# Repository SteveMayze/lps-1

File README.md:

# Solar Power Sensor LPS-1

A simple remote sensing node to monitor the voltage and load current for a solar/battery unit.
This unit brings together the prototype projects [Gateway Node](https://github.com/SteveMayze/leawood_gateway),  [Atmega1608 Development board](https://github.com/SteveMayze/atmega1608_dev) and [Sensor node firmware (Atmega1608 and INA219)](https://github.com/SteveMayze/PowerSensor-Atmega1608) to create a unified PCB that can be deployed to the field to make a connection to the gateway project in order to transfer the sensor data to the internet.

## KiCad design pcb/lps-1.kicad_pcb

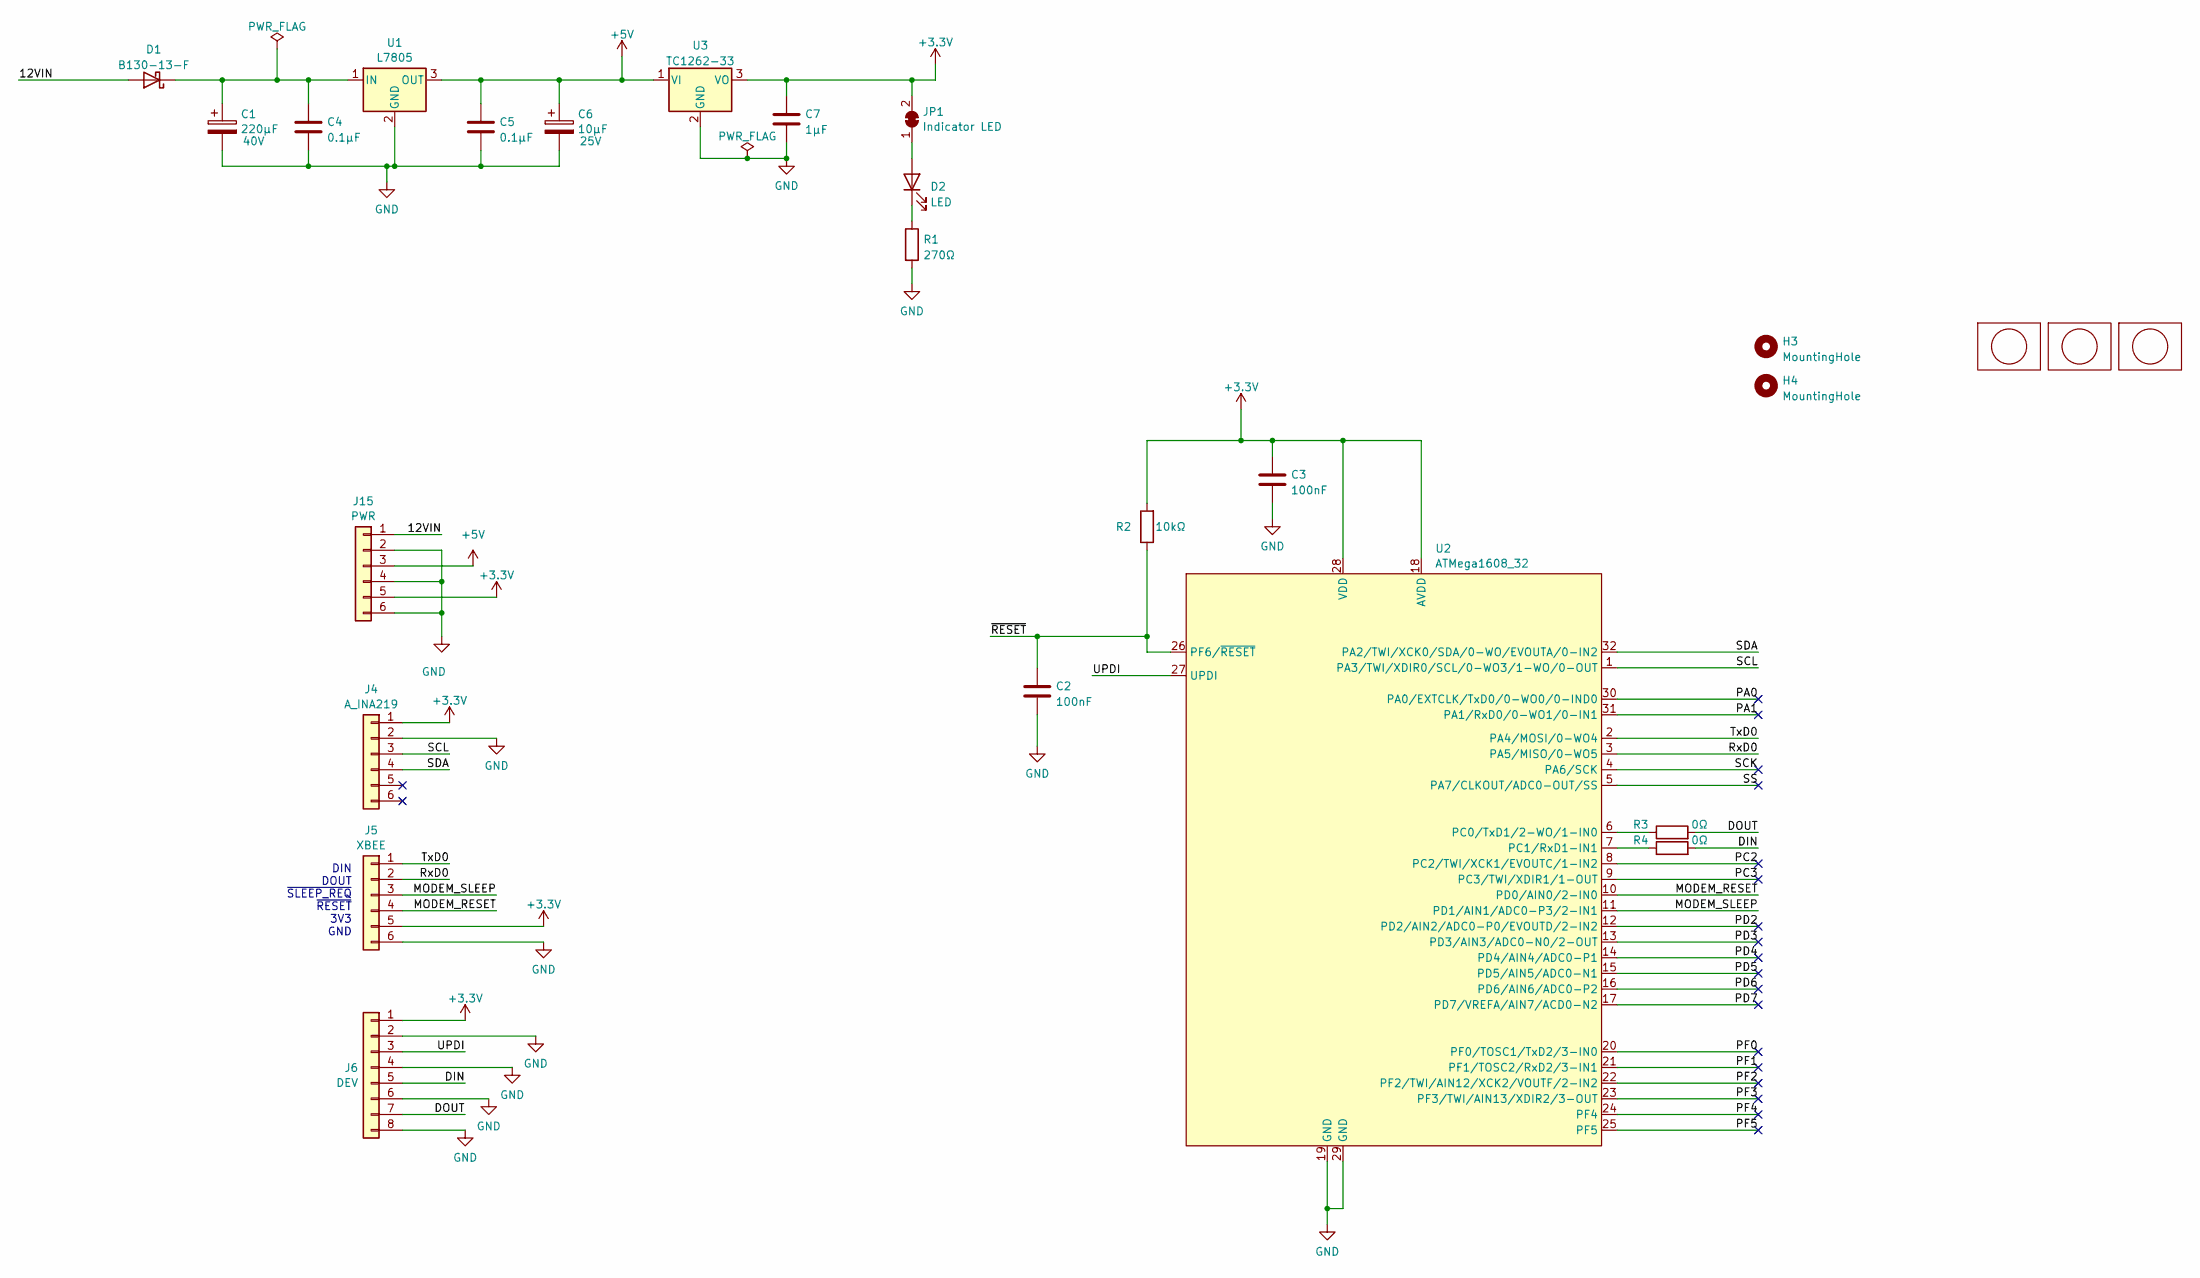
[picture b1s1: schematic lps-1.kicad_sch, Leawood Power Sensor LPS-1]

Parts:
C1: 220μF; CP_Radial_D10.0mm_P2.50mm; Voltage 40V
C2, C3: 100nF; C_0805_2012Metric
C4, C5: 0.1μF; C_0805_2012Metric_Pad1.18x1.45mm_HandSolder
C6: 10μF; CP_Radial_D5.0mm_P2.50mm; Voltage 25V
C7: 1μF; C_0805_2012Metric_Pad1.18x1.45mm_HandSolder
D1: B130-13-F; D_SMA; MPN B130-13-F
D2: LED; LED_0805_2012Metric
H3, H4: MountingHole; MountingHole_2.7mm_M2.5
J4: A_INA219; Adafruit-INA219_2xM2.5
J5: XBEE; PinHeader_2x03_P2.54mm_Vertical
J6: DEV; PinHeader_1x08_P2.54mm_Vertical
J15: PWR; PinHeader_1x06_P2.54mm_Vertical
JP1: Indicator LED; SolderJumper-2_P1.3mm_Bridged_RoundedPad1.0x1.5mm
Lg1, Lg2: logo; MyBasic_rounded_50_1
Lg3: logo; KiCad-Logo_5mm_SilkScreen
R1: 270Ω; R_0805_2012Metric
R2: 10kΩ; R_0805_2012Metric
R3, R4: 0Ω; R_0805_2012Metric
U1: L7805; TO-220-3_Vertical
U2: ATMega1608_32; TQFP-32_7x7mm_P0.8mm
U3: TC1262-33; SOT-223-3_TabPin2

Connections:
+3.3V: C3.1, C7.1, J4.1, J5.5, J6.1, J15.5, JP1.2 (B), R2.2, U2.18 (AVDD), U2.28 (VDD), U3.3 (VO)
+5V: C5.1, C6.1, J15.3, U1.3 (OUT), U3.1 (VI)
/12VIN: D1.2 (A), J15.1
/DIN: J6.5, R4.2
/DOUT: J6.7, R3.2
/MODEM_RESET: J5.4, U2.10 (PD0/AIN0/2-IN0)
/MODEM_SLEEP: J5.3, U2.11 (PD1/AIN1/ADC0-P3/2-IN1)
/PA0: U2.30 (PA0/EXTCLK/TxD0/0-WO0/0-IND0)
/PA1: U2.31 (PA1/RxD0/0-WO1/0-IN1)
/PC2: U2.8 (PC2/TWI/XCK1/EVOUTC/1-IN2)
/PC3: U2.9 (PC3/TWI/XDIR1/1-OUT)
/PD2: U2.12 (PD2/AIN2/ADC0-P0/EVOUTD/2-IN2)
/PD3: U2.13 (PD3/AIN3/ADC0-N0/2-OUT)
/PD4: U2.14 (PD4/AIN4/ADC0-P1)
/PD5: U2.15 (PD5/AIN5/ADC0-N1)
/PD6: U2.16 (PD6/AIN6/ADC0-P2)
/PD7: U2.17 (PD7/VREFA/AIN7/ACD0-N2)
/PF0: U2.20 (PF0/TOSC1/TxD2/3-IN0)
/PF1: U2.21 (PF1/TOSC2/RxD2/3-IN1)
/PF2: U2.22 (PF2/TWI/AIN12/XCK2/VOUTF/2-IN2)
/PF3: U2.23 (PF3/TWI/AIN13/XDIR2/3-OUT)
/PF4: U2.24 (PF4)
/PF5: U2.25 (PF5)
/RxD0: J5.2, U2.3 (PA5/MISO/0-WO5)
/SCK: U2.4 (PA6/SCK)
/SCL: J4.3, U2.1 (PA3/TWI/XDIR0/SCL/0-WO3/1-WO/0-OUT)
/SDA: J4.4, U2.32 (PA2/TWI/XCK0/SDA/0-WO/EVOUTA/0-IN2)
/SS: U2.5 (PA7/CLKOUT/ADC0-OUT/SS)
/TxD0: J5.1, U2.2 (PA4/MOSI/0-WO4)
/UPDI: J6.3, U2.27 (UPDI)
/~RESET: C2.1, R2.1, U2.26 (PF6/~RESET)
GND: C1.2, C2.2, C3.2, C4.2, C5.2, C6.2, C7.2, J4.2, J5.6, J6.2, J6.4, J6.6, J6.8, J15.2, J15.4, J15.6, R1.2, U1.2 (GND), U2.19 (GND), U2.29 (GND), U3.2 (GND)
unnamed: C1.1, C4.1, D1.1 (K), U1.1 (IN)
unnamed: D2.2 (A), JP1.1 (A)
unnamed: D2.1 (K), R1.1
unnamed: R3.1, U2.6 (PC0/TxD1/2-WO/1-IN0)
unnamed: R4.1, U2.7 (PC1/RxD1-IN1)

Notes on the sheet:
DIN DOUT ~{SLEEP_REQ} ~{RESET} 3V3 GND

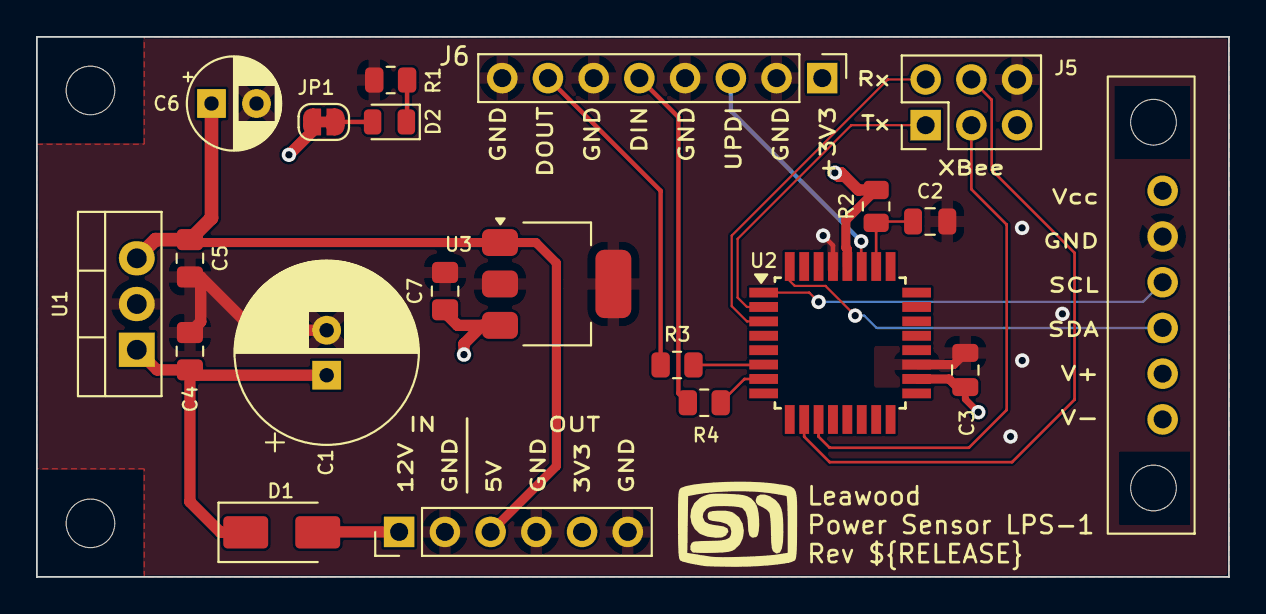
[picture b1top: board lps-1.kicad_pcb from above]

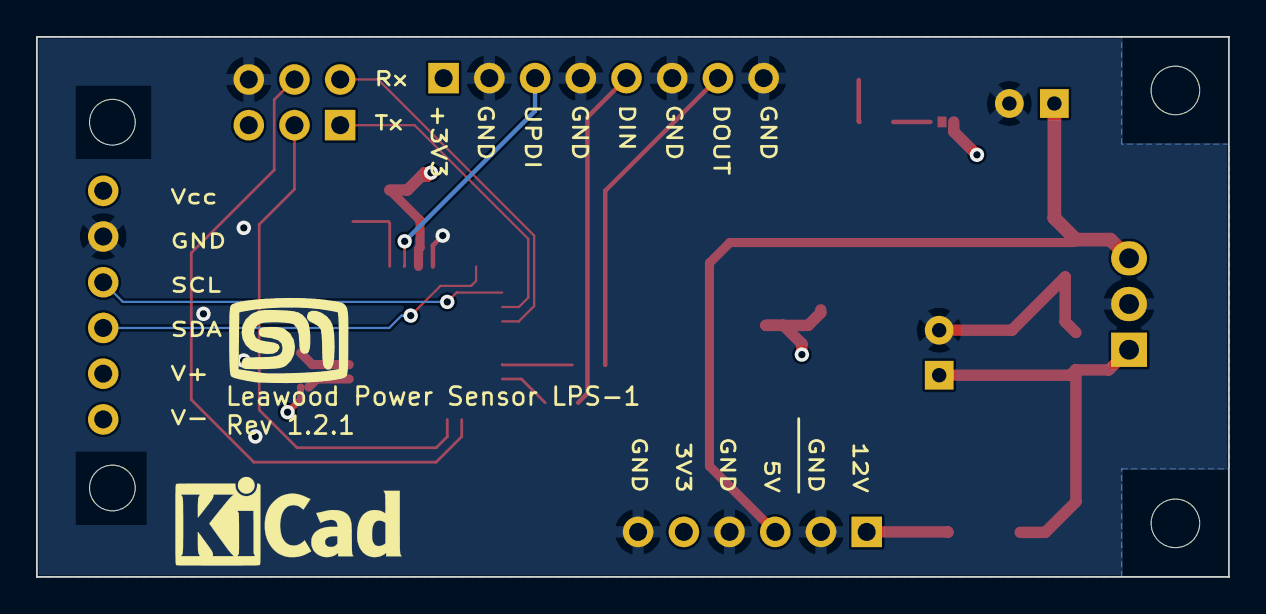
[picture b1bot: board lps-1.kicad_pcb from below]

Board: 4 copper layers, 66.2 x 30.0 mm, 26 parts (2 on the bottom side), 19 nets.

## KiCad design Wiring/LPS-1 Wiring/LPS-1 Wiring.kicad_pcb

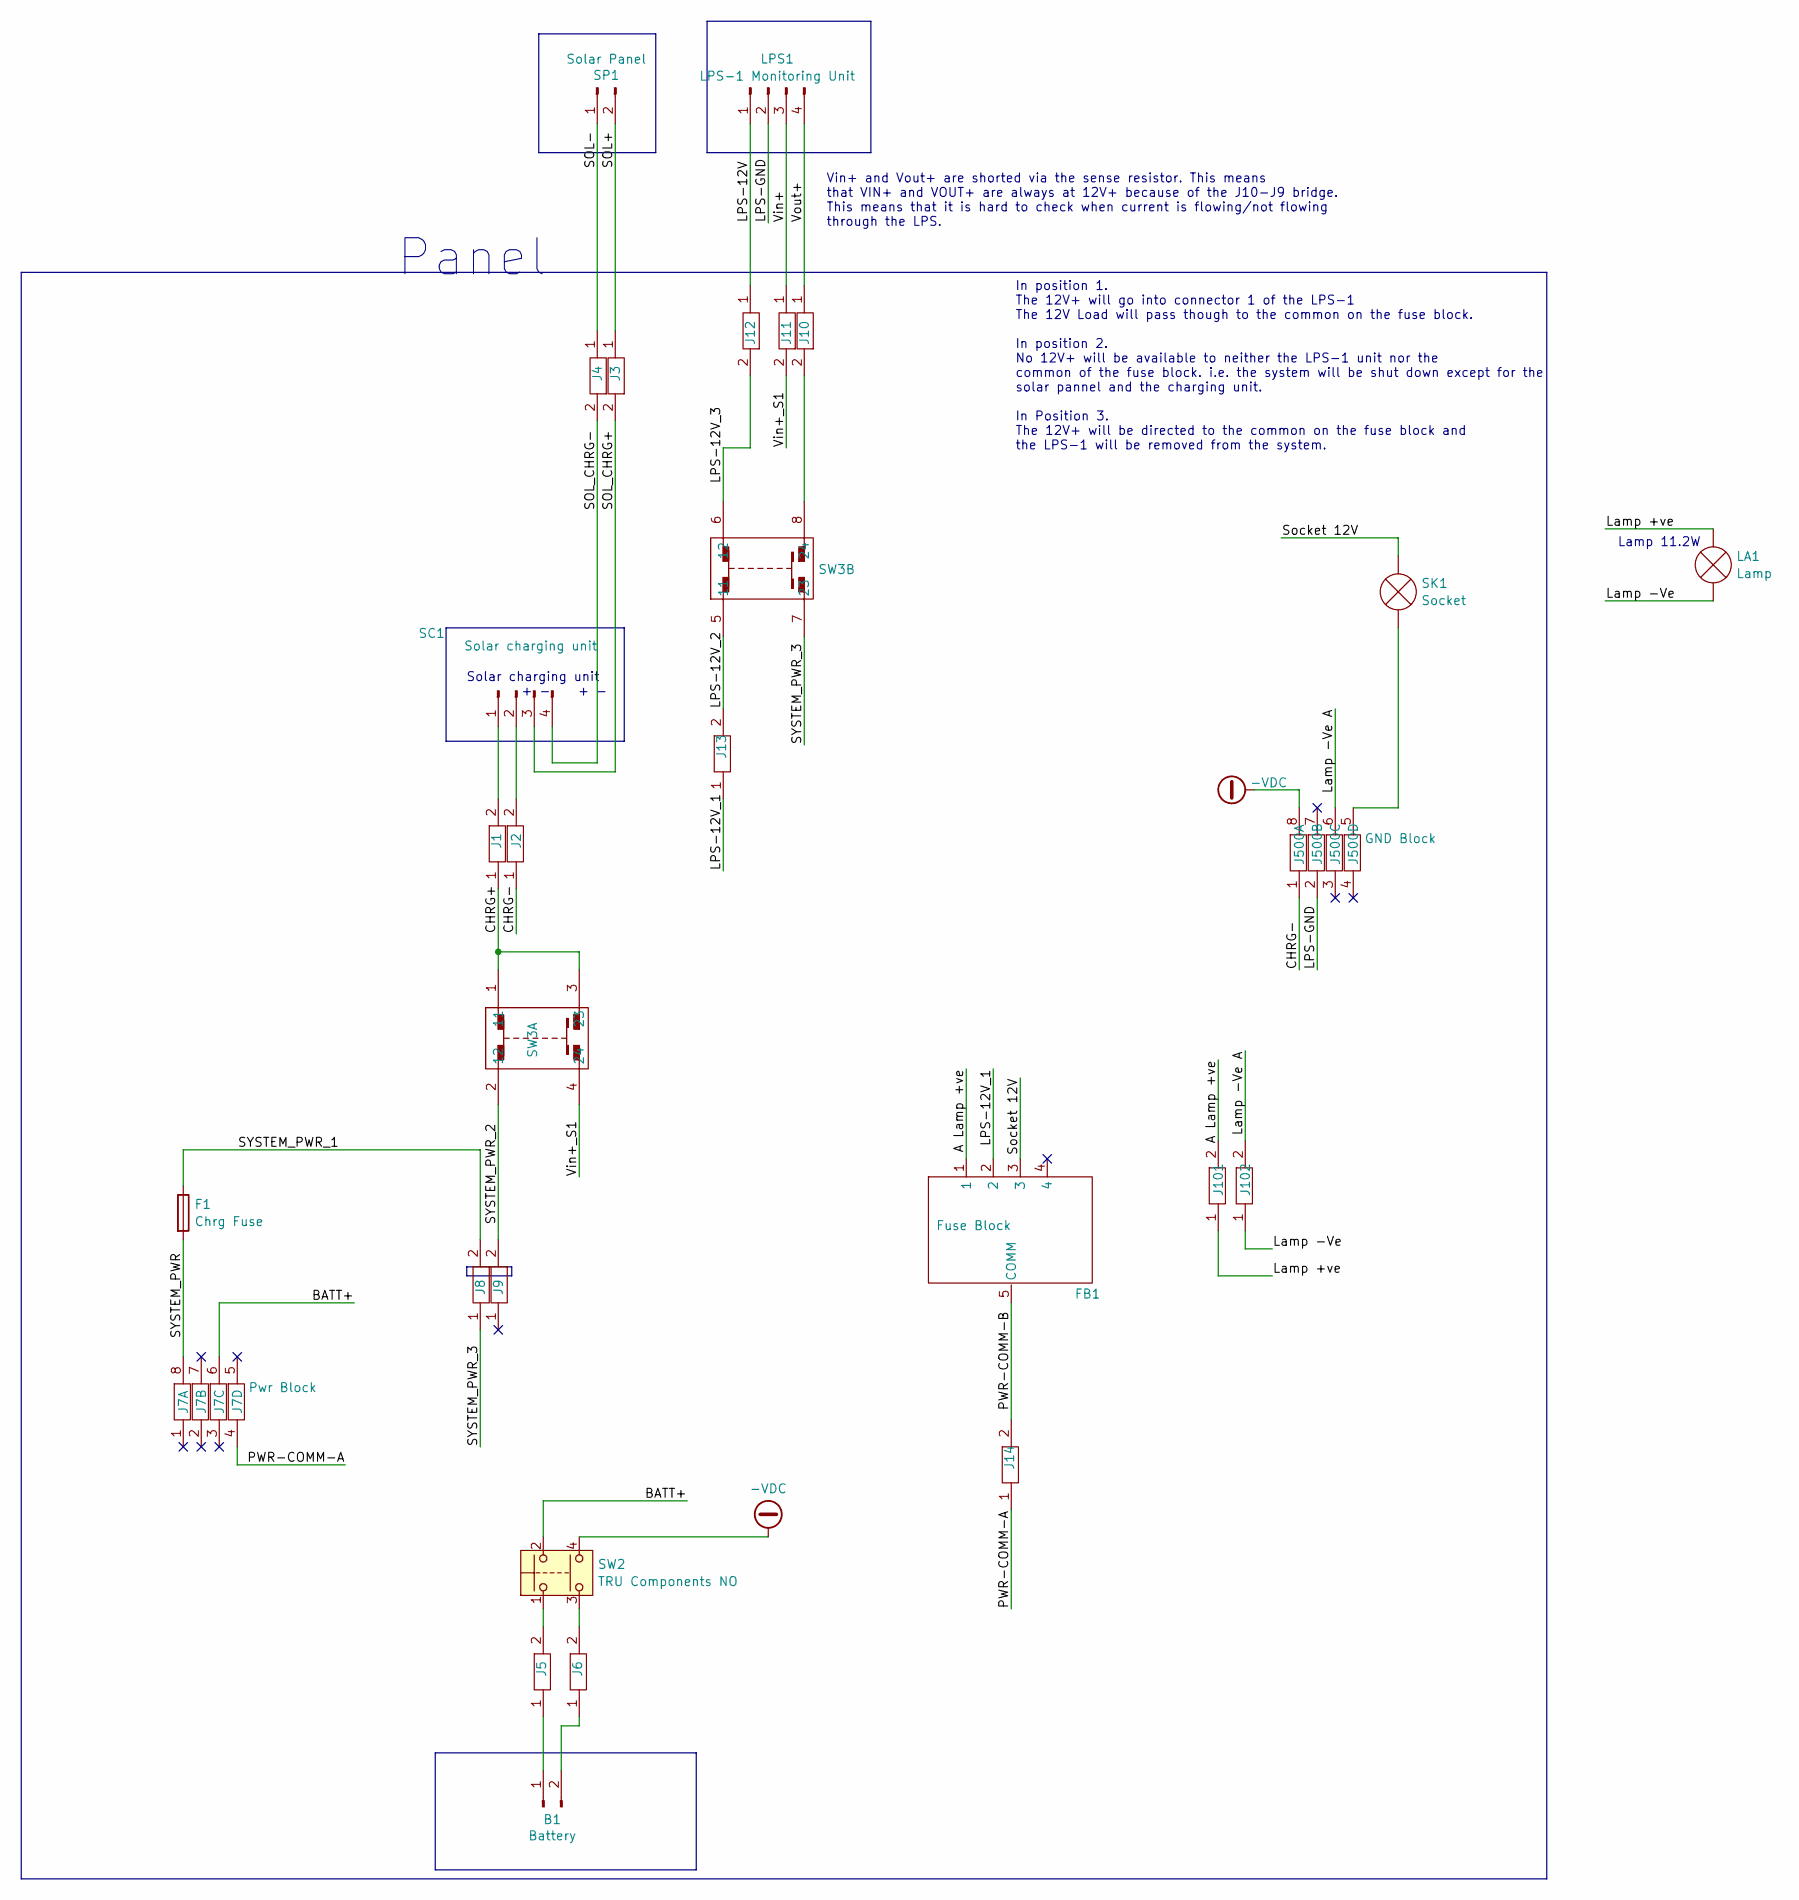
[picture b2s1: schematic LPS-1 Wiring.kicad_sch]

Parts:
B1: Battery; PinHeader_1x02_P2.54mm_Vertical
F1: Chrg Fuse; PinHeader_1x02_P2.54mm_Vertical
FB1: Fuse Block; FUSE_BLOCK_TRU_COMPONENTS-TC-9070396
J1, J2, J3, J4, J5, J6, J8, J9, J10, J11, J12, J13, J14, J101, J102: Block_Connector_01_b; Degson_01_PC2.5-01P-11-00AH-1_5.2
J7: Pwr Block; Degson_04_Bridged-PC2.5-01P-11-00AH-1_5.2
J500: GND Block; Degson_04_Bridged-PC2.5-01P-11-00AH-1_5.2
LA1: Lamp; PinHeader_1x02_P2.54mm_Vertical
LPS1: LPS-1 Monitoring Unit; LPS-1_EXT_PWR
SC1: Solar charging unit; H-TRONIC Solar-Lageregler
SK1: Socket; PinHeader_1x02_P2.54mm_Vertical
SP1: Solar Panel; PinHeader_1x02_P2.54mm_Vertical
SW2: TRU Components NO; TruComponents_SW_LAS0_1
SW3: TruComponents_SW_LAS0

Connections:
-VDC: J500.8, SW2.4 (24)
/A Lamp +ve: FB1.1, J101.2
/BATT+: J7.6, SW2.2 (12)
/CHRG+: J1.1, SW3.1 (11), SW3.3 (23)
/CHRG-: J2.1, J500.1
/LPS-12V: J12.1, LPS1.1
/LPS-12V_1: FB1.2, J13.1
/LPS-12V_2: J13.2, SW3.5 (11)
/LPS-12V_3: J12.2, SW3.6 (12)
/LPS-GND: J500.2, LPS1.2
/Lamp +ve: J101.1, LA1.2 (+)
/Lamp -Ve: J102.1, LA1.1 (-)
/Lamp -Ve A: J102.2, J500.6
/PWR-COMM-A: J7.4, J14.1
/PWR-COMM-B: FB1.5 (COMM), J14.2
/SOL+: J3.1, SP1.2
/SOL-: J4.1, SP1.1
/SOL_CHRG+: J3.2, SC1.3
/SOL_CHRG-: J4.2, SC1.4
/SYSTEM_PWR: F1.2, J7.8
/SYSTEM_PWR_1: F1.1, J8.2
/SYSTEM_PWR_2: J9.2, SW3.2 (12)
/SYSTEM_PWR_3: J8.1, SW3.7 (23)
/Socket 12V: FB1.3, SK1.2 (+)
/VIN+: J11.1, LPS1.3
/VIN-: J10.1, LPS1.4
/Vin+_S1: J11.2, SW3.4 (24)
unnamed: B1.1, J5.1
unnamed: B1.2, J6.1
unnamed: J1.2, SC1.1
unnamed: J2.2, SC1.2
unnamed: J500.5, SK1.1 (-)
unnamed: J5.2, SW2.1 (11)
unnamed: J6.2, SW2.3 (23)
unnamed: J10.2, SW3.8 (24)

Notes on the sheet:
Vin+ and Vout+ are shorted via the sense resistor. This means that VIN+ and VOUT+ are always at 12V+ because of the J10-J9 bridge. This means that it is hard to check when current is flowing/not flowing through the LPS.
In position 1. The 12V+ will go into connector 1 of the LPS-1 The 12V Load will pass though to the common on the fuse block. In position 2. No 12V+ will be available to neither the LPS-1 unit nor the common of the fuse block. i.e. the system will be shut down except for the solar pannel and the cha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
Solar charging unit + - + -
Lamp 11.2W
Panel

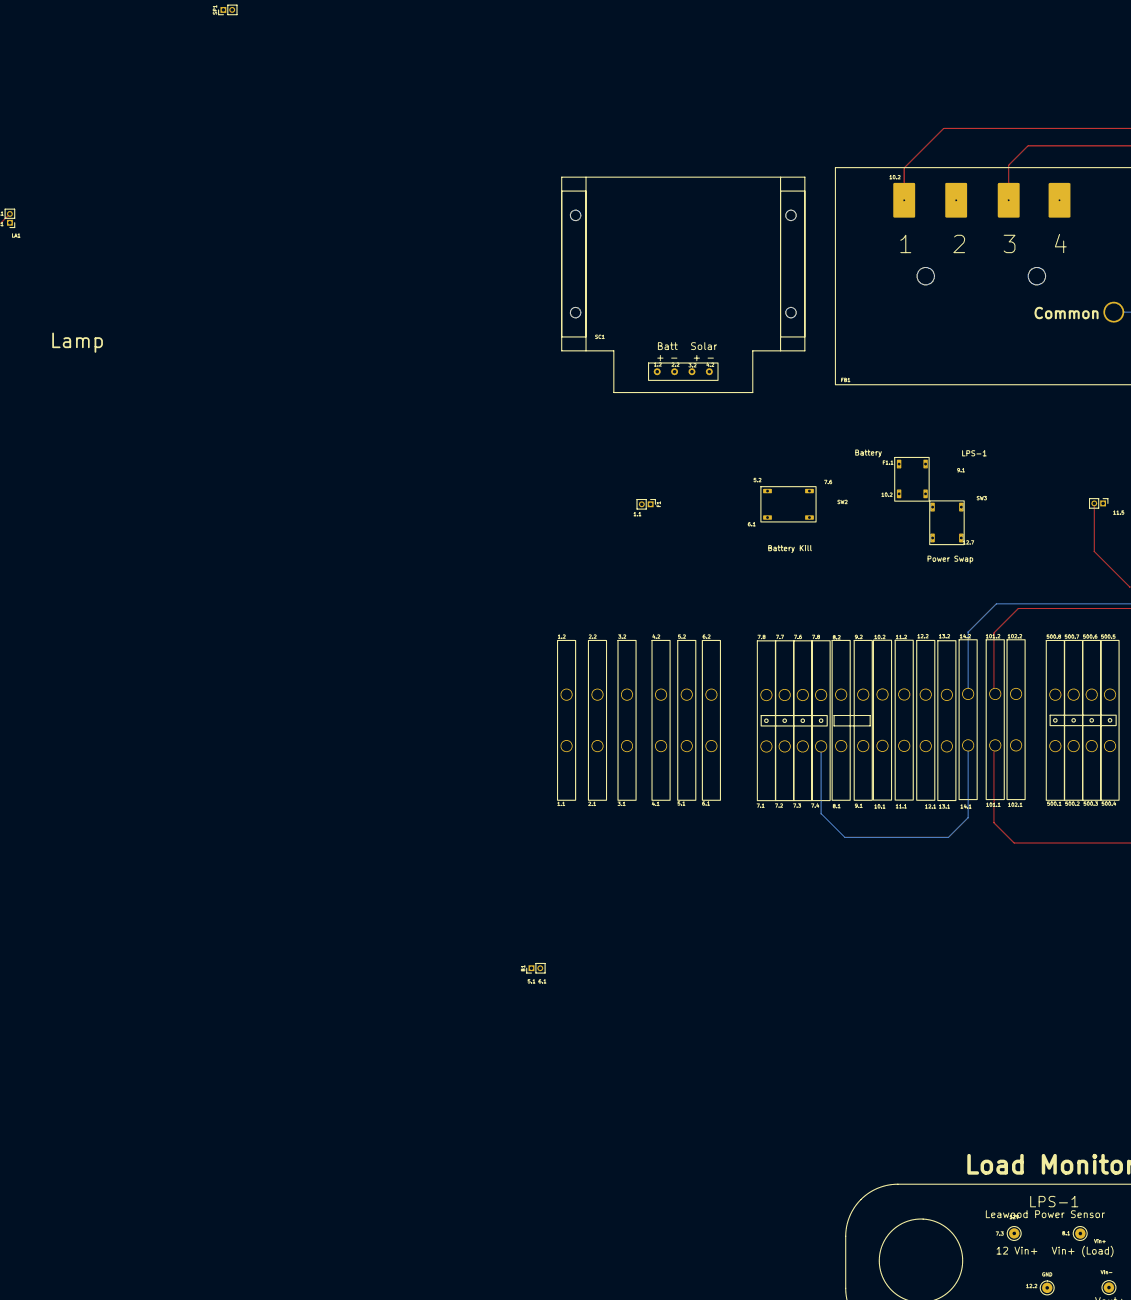
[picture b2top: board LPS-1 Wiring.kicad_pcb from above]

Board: 32 copper layers, 27 parts (0 on the bottom side), 35 nets.

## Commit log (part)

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2024-01-02 Started the KiCad project
2024-01-28 First layout
2024-03-12 Refactored the connectors for the LPS-X-1
2024-03-13 Reduces the board footprint and introduces copper fills on F and B
2024-03-22 Rework to include a 5V LDO
2024-03-26 Reworked the connectors
2024-04-16 Revision 1.0
2024-04-21 sync
2024-04-25 Fixes the drill holes for the INA219
2024-04-26 Revision 1.01 Gerbers
2024-05-12 Correction to the TWI0 pin selection
2024-05-15 Created keep out zones around the mounting holes
2025-03-08 Update and sync
2025-12-09 Adds wiring diagram
2025-12-09 Adds the artwork for the LPS-1
2025-12-09 Chagnes to the panel layout
2026-05-22 Moved the design to KiCad 10
2026-05-23 Update to the connection block symols and footprints
2026-05-24 Adds a firmware architecture block diagram
2026-06-04 Adds release script
2026-06-04 Updated the wiring diagram
2026-06-04 Refactored the reference numbering
2026-06-08 Refactored the nomenclature for non-connector components
2026-06-12 Updates to the wriging layout
2026-06-13 Reconfigured the LPS-1 wiring
2026-06-16 Panel wiring update
2026-06-17 Local update
2026-06-17 Fz update
